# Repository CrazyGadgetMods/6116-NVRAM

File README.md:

# 6116 NVRAM

This is an opensource NVRAM replacement for 6116 RAM used in Williams System 11 / System 9, Bally System 9, and some Data East games.  

I did not make an official BOM for this since there are so few components.  
The values are as follows (with DigiKey hyperlinks):  
U1: [FM16W08-SG](https://www.digikey.com/en/products/detail/infineon-technologies/FM16W08-SG/4090348)  
C1: [10µF 0603 16V](https://www.digikey.com/en/products/detail/samsung-electro-mechanics/CL10X106MO8NRNC/5961253) (or equivalent)  
R1, R2: [10kΩ 0603 1%](https://www.digikey.com/en/products/detail/bourns-inc/CR0603-FX-1002ELF/3593188) (or equivalent)  
Headers (x2): [12-Pin Header 0.1" (2.54mm) pitch](https://www.digikey.com/en/products/detail/adam-tech/PH1-12-UA/9830395) (or equivalent)  
IC Socket: [24-Pin DIP Socket 0.1" (2.54mm) pitch](https://www.digikey.com/en/products/detail/adam-tech/ICS-624-T/9832867) (or equivalent)  

Renders:  

Assembled Board:  

Installation in Williams System 11 Grand Lizard:  

## Credits
- SonnyJim: Helping me understand how to transpose the FM16W08 to a 6116 pinout.
- [Pinball People Discord](https://discord.com/invite/XffPx6VKTv): Being a wonderful, helpful community.
- [Pinside](https://pinside.com/): Being the best pinball community out there, and a cornucopia of knowledge!

## License
Solderpad Hardware License v2.1

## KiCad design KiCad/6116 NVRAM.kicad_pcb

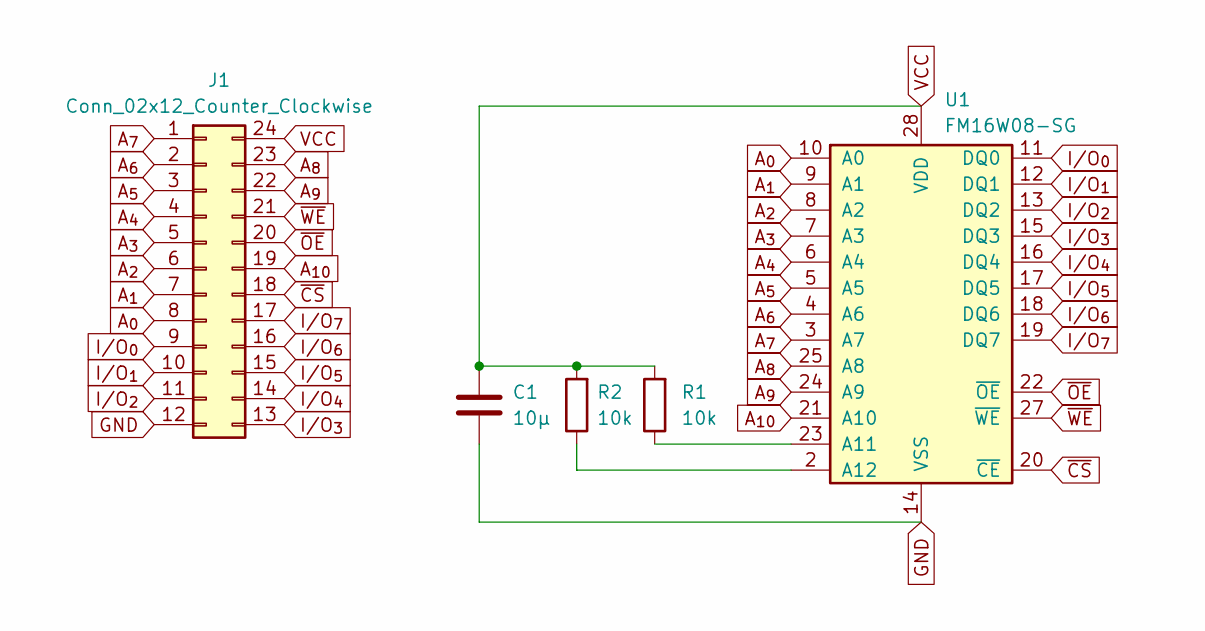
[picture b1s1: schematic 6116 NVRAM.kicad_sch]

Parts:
C1: 10µ; C_0603_1608Metric_Pad1.08x0.95mm_HandSolder
J1: Conn_02x12_Counter_Clockwise; DIP-24_W15.24mm
R1, R2: 10k; R_0603_1608Metric_Pad0.98x0.95mm_HandSolder
U1: FM16W08-SG; SOIC-28W_7.5x17.9mm_P1.27mm

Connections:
A_{0}: J1.8, U1.10 (A0)
A_{1}: J1.7, U1.9 (A1)
A_{2}: J1.6, U1.8 (A2)
A_{3}: J1.5, U1.7 (A3)
A_{4}: J1.4, U1.6 (A4)
A_{5}: J1.3, U1.5 (A5)
A_{6}: J1.2, U1.4 (A6)
A_{7}: J1.1, U1.3 (A7)
A_{8}: J1.23, U1.25 (A8)
A_{9}: J1.22, U1.24 (A9)
A_{10}: J1.19, U1.21 (A10)
GND: C1.2, J1.12, U1.14 (VSS)
I/O_{0}: J1.9, U1.11 (DQ0)
I/O_{1}: J1.10, U1.12 (DQ1)
I/O_{2}: J1.11, U1.13 (DQ2)
I/O_{3}: J1.13, U1.15 (DQ3)
I/O_{4}: J1.14, U1.16 (DQ4)
I/O_{5}: J1.15, U1.17 (DQ5)
I/O_{6}: J1.16, U1.18 (DQ6)
I/O_{7}: J1.17, U1.19 (DQ7)
unnamed: R1.1, U1.23 (A11)
unnamed: R2.1, U1.2 (A12)
VCC: C1.1, J1.24, R1.2, R2.2, U1.28 (VDD)
~CS: J1.18, U1.20 (~CE)
~OE: J1.20, U1.22 (~OE)
~WE: J1.21, U1.27 (~WE)

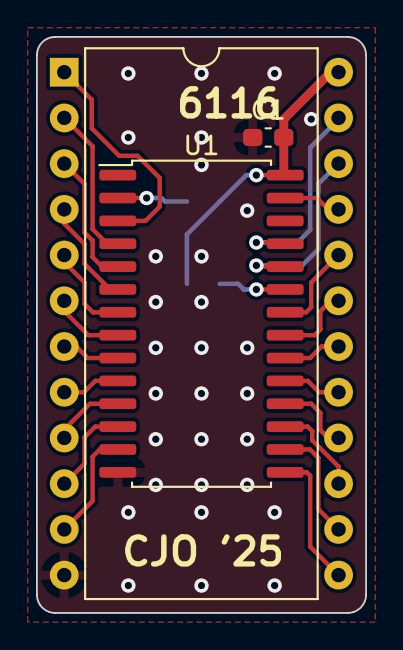
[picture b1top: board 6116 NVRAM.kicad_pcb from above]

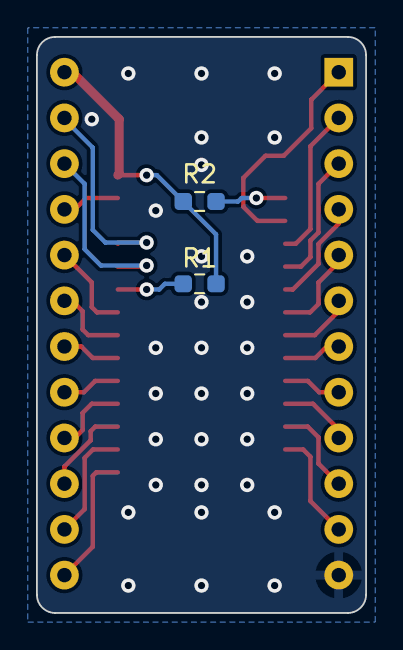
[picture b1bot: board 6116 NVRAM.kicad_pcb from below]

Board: 2 copper layers, 18.3 x 32.0 mm, 5 parts (2 on the bottom side), 26 nets.
